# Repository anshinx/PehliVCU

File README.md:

# Pehlivan VCU (Vehicle Control Unit) - REVO.1 🏎️⚡

Trakya Üniversitesi Pehlivan Team ve Tas-Pro (Tasarım ve Proje Topluluğu) bünyesinde Shell Eco-marathon yarış aracı için özel olarak geliştirilmiş, endüstriyel standartlarda **Araç Kontrol Ünitesi (VCU)** donanım ve gömülü yazılım projesidir.

Bu kart; verimlilik, hafiflik ve kurşungeçirmez gürültü bağışıklığı (EMI/EMC) felsefesiyle, geleneksel ağır komponentlerin (lineer regülatörler, taş dirençler vb.) yerini tamamen akıllı yazılımsal ve anahtarlamalı çözümlere bırakması amacıyla sıfırdan tasarlanmıştır.

---

## 🛠️ Teknik Özellikler & Donanım Mimarisi

* **Ana İşlemci:** STM32G431 (ARM Cortex-M4 @170MHz, Matematik Hızlandırıcı CORDIC & FMAC).
* **Güç Girişi:** 12V - 14.4V Yarış Aküsü (Doğrudan besleme).
* **Periferi Beslemeleri:** * Yeni nesil yüksek verimli anahtarlamalı güç katı.
  * Nextion HMI, LoRa ve SD Kart modülleri için `100nF` seramik ve `10µF` kutuplu elektrolitik filtre kombinasyonlu izole besleme hatları.
* **Güç Çıkışları (Sürücü Katı):** `BTS432` Akıllı Güç Anahtarları (Far, Sinyal ve Fren Lambası kontrolü için).
* **Haberleşme & Telemetri:** * Doğrudan işlemciye bağlı LoRa Modülü (Kablosuz Telemetri).
  * Nextion HMI Ekran Arayüzü (UART).
  * FDCAN (Geriye dönük klasik CAN-Bus uyumlu, pitte maksimum esneklik).
* **Veri Günlüğü (Data Logging):** SD Kart Modülü üzerinden SPI haberleşmeli, anlık veri kaybını engelleyen "Kara Kutu" loglama altyapısı.
* **Zaman Senkronizasyonu:** CR2032/Düğme Pil destekli dahili RTC (Real Time Clock) mimarisi.

---

## ⚡ Donanım Tasarım Radikalleri (Neden REVO.1?)

REVO.1 revizyonu, pitteki kriz anlarını ve araç içi verimliliği maksimuma çıkarmak için şu kritik donanımsal kararlarla şekillendirilmiştir:

1. **Sıfır Taş Direnç / Sıfır Isı:** Şerit LED'lerin akım sınırlaması için kaba ve el yakan taş dirençler kullanılmamıştır. Akım kontrolü, STM32'nin Timer birimleri üzerinden **yazılımsal PWM (Sinyal Genişlik Modülasyonu)** ile çözülmüştür. Akü 14.4V'a vurduğunda lamba hatları `%83 Duty Cycle` ile kilitlenerek ortalama akım ideal 12V seviyesine çekilir.
2. **Yüksek Titreşim Dayanımı:** Kart üzerindeki 16 MHz harici kristal katında, yarış esnasındaki vibrasyondan bacakların yorulup kopmasını engellemek amacıyla bacaklı kılıflar yerine **Raltron 3225 4-SMD (RH100-16.000-18-2020-TR)** seramik kılıf tercih edilmiştir. Kristal yük kapasitesi ($C_L = 18\text{pF}$) hesaba katılarak hatlar `26pF` (veya `22pF`/`27pF`) kondansatörlerle stabilize edilmiştir.
3. **Parazit Bağışıklığı & Reset Koruması:** Araç içi motor sürücülerin ve yüksek akım hatlarının yaratacağı manyetik gürültülerden (EMI) korunmak için `NRST` (Reset) pini harici **10 kΩ dirençle `+3V3` hattına asılmış (Pull-Up)** ve `100nF` kondansatör ile şaseye filtrelenmiştir.
4. **Çift Katmanlı Bakır Havuzu:** Gürültü bağışıklığı için Bottom Layer tamamen kesintisiz `GND` bakır dolgusuyla kaplanmış, Top Layer ise STM32 etrafında `3V3` güç adalarıyla zırhlandırılmıştır.

---

## 🛰️ Gecikme (Latency) & Telemetri Lojiği

Kart üzerindeki pil destekli RTC donanımı, pit duvarı ile araç arasındaki LoRa veri transferinin gecikme süresini (latency) milisaniyelik çözünürlükle hesaplamak için kullanılır:
* Araç çalıştırılmadan önce bilgisayardan (veya Nextion üzerinden) Unix Epoch Time sinyaliyle RTC eşitlenir.
* VCU, LoRa paketini fırlatırken Unix zaman damgasının arkasına `HAL_GetTick()` değerinin son 3 basamağını ekler (`[UnixTimestamp].[Milisaniye]`).
* Pit tarafındaki alıcı yazılım, paketin varış zamanı ile paket içindeki zaman damgasını çıkararak hattaki milisaniyelik gecikmeyi anlık olarak raporlar.

---

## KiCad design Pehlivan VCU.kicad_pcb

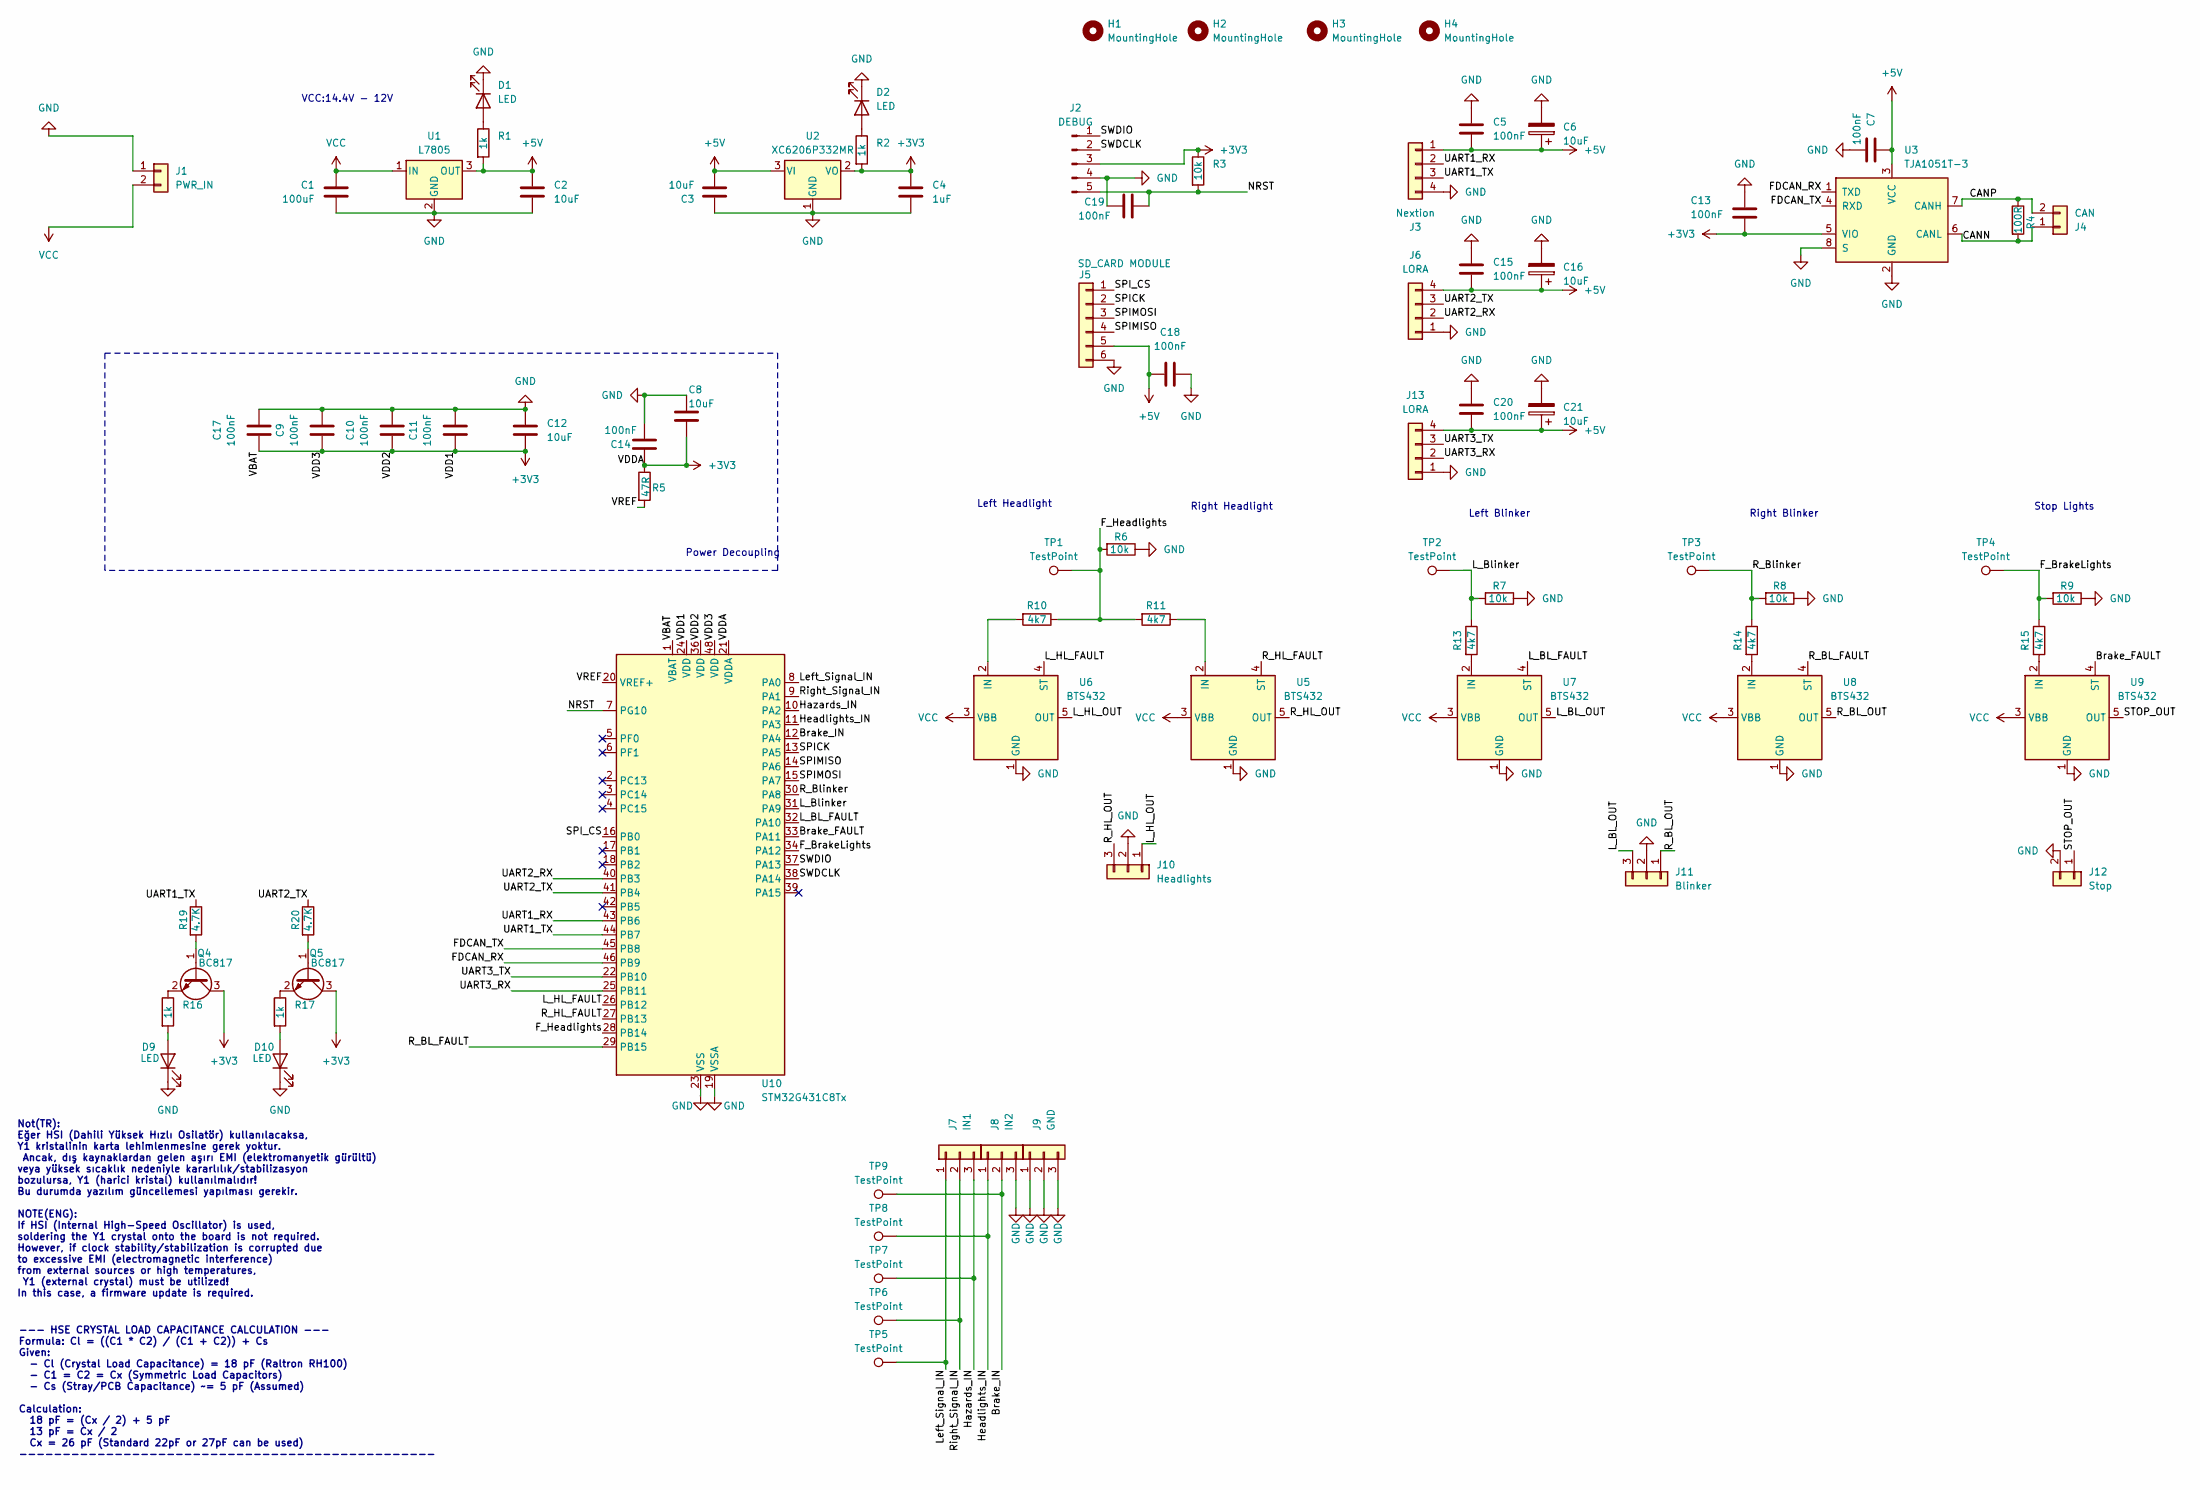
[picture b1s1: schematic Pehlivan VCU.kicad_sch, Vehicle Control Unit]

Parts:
C1: 100uF; C_Radial_D4.0mm_H7.0mm_P1.50mm
C2, C3, C6, C16, C21: 10uF; C_Radial_D5.0mm_H5.0mm_P2.00mm
C4: 1uF; C_Radial_D5.0mm_H5.0mm_P2.00mm
C5, C15, C18, C19, C20: 100nF; C_0805_2012Metric_Pad1.18x1.45mm_HandSolder
C7, C13: 100nF; C_1210_3225Metric_Pad1.33x2.70mm_HandSolder
C8: 10uF; C_0805_2012Metric_Pad1.18x1.45mm_HandSolder
C9, C10, C11, C14, C17: 100nF; C_0603_1608Metric
C12: 10uF; C_1210_3225Metric_Pad1.33x2.70mm_HandSolder
D1, D2, D9, D10: LED; LED_1206_3216Metric_Pad1.42x1.75mm_HandSolder
H1, H2, H3, H4: MountingHole; MountingHole_2.7mm_M2.5_DIN965_Pad
J1: PWR_IN; TerminalBlock_Phoenix_MKDS-1,5-2-5.08_1x02_P5.08mm_Horizont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
J2: DEBUG; PinHeader_1x05_P2.54mm_Vertical
J3: Nextion; TerminalBlock_Phoenix_MKDS-1,5-4-5.08_1x04_P5.08mm_Horizont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
J4: CAN; TerminalBlock_Phoenix_MKDS-1,5-2-5.08_1x02_P5.08mm_Horizont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
J5: SD_CARD MODULE; PinSocket_1x06_P2.54mm_Vertical
J6, J13: LORA; PinSocket_1x04_P2.54mm_Horizontal
J7: IN1; TerminalBlock_Phoenix_MKDS-1,5-3-5.08_1x03_P5.08mm_Horizont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
J8: IN2; TerminalBlock_Phoenix_MKDS-1,5-3-5.08_1x03_P5.08mm_Horizont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
J9: GND; TerminalBlock_Phoenix_MKDS-1,5-3-5.08_1x03_P5.08mm_Horizont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
J10: Headlights; TerminalBlock_Phoenix_MKDS-1,5-3-5.08_1x03_P5.08mm_Horizont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
J11: Blinker; TerminalBlock_Phoenix_MKDS-1,5-3-5.08_1x03_P5.08mm_Horizont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
J12: Stop; TerminalBlock_Phoenix_MKDS-1,5-2-5.08_1x02_P5.08mm_Horizont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
Q4, Q5: BC817; SOT-23
R1, R2, R16, R17: 1k; R_0805_2012Metric
R3, R6, R7, R8, R9: 10k; R_0805_2012Metric
R4: 100R; R_0805_2012Metric
R5: 47R; R_0603_1608Metric_Pad0.98x0.95mm_HandSolder
R10, R11, R13, R14, R15: 4k7; R_0805_2012Metric
R19, R20: 4.7K; R_0805_2012Metric_Pad1.20x1.40mm_HandSolder
TP1, TP2, TP3, TP4, TP5, TP6, TP7, TP8, TP9: TestPoint; TestPoint_Pad_D1.0mm
U1: L7805; TO-220-3_Vertical
U2: XC6206P332MR; SOT-23-3
U3: TJA1051T-3; SOIC-8_3.9x4.9mm_P1.27mm
U5, U6, U7, U8, U9: BTS432; TO-263-4
U10: STM32G431C8Tx; LQFP-48_7x7mm_P0.5mm

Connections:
+3V3: C4.1, C8.2, C9.1, C10.1, C11.1, C12.2, C13.2, C14.1, C17.1, J2.3, Q4.3 (C), Q5.3 (C), R2.2, R3.1, R5.1, U2.2 (VO), U3.5 (VIO), U10.1 (VBAT), U10.21 (VDDA), U10.24 (VDD), U10.36 (VDD), U10.48 (VDD)
+5V: C2.1, C3.1, C5.2, C6.1, C7.1, C15.2, C16.1, C18.2, C20.2, C21.1, J3.1, J5.5, J6.4, J13.4, R1.2, U1.3 (OUT), U2.3 (VI), U3.3 (VCC)
/Brake_FAULT: U9.4 (ST), U10.33 (PA11)
/Brake_IN: J8.2, TP9.1 (1_1), U10.12 (PA4)
/CANN: J4.1, R4.2, U3.6 (CANL)
/CANP: J4.2, R4.1, U3.7 (CANH)
/FDCAN_RX: U3.1 (TXD), U10.46 (PB9)
/FDCAN_TX: U3.4 (RXD), U10.45 (PB8)
/F_BrakeLights: R9.2, R15.1, TP4.1 (1_1), U10.34 (PA12)
/F_Headlights: R6.2, R10.1, R11.2, TP1.1 (1_1), U10.28 (PB14)
/Hazards_IN: J7.3, TP7.1 (1_1), U10.10 (PA2)
/Headlights_IN: J8.1, TP8.1 (1_1), U10.11 (PA3)
/L_BL_FAULT: U7.4 (ST), U10.32 (PA10)
/L_BL_OUT: J11.3, U7.5 (OUT)
/L_Blinker: R7.2, R13.1, TP2.1 (1_1), U10.31 (PA9)
/L_HL_FAULT: U6.4 (ST), U10.26 (PB12)
/L_HL_OUT: J10.1, U6.5 (OUT)
/Left_Signal_IN: J7.1, TP5.1 (1_1), U10.8 (PA0)
/NRST: C19.1, J2.5, R3.2, U10.7 (PG10)
/R_BL_FAULT: U8.4 (ST), U10.29 (PB15)
/R_BL_OUT: J11.1, U8.5 (OUT)
/R_Blinker: R8.2, R14.1, TP3.1 (1_1), U10.30 (PA8)
/R_HL_FAULT: U5.4 (ST), U10.27 (PB13)
/R_HL_OUT: J10.3, U5.5 (OUT)
/Right_Signal_IN: J7.2, TP6.1 (1_1), U10.9 (PA1)
/SPICK: J5.2, U10.13 (PA5)
/SPIMISO: J5.4, U10.14 (PA6)
/SPIMOSI: J5.3, U10.15 (PA7)
/SPI_CS: J5.1, U10.16 (PB0)
/STOP_OUT: J12.1, U9.5 (OUT)
/SWDCLK: J2.2, U10.38 (PA14)
/SWDIO: J2.1, U10.37 (PA13)
/UART1_RX: J3.2, U10.43 (PB6)
/UART1_TX: J3.3, R19.1, U10.44 (PB7)
/UART2_RX: J6.2, U10.40 (PB3)
/UART2_TX: J6.3, R20.1, U10.41 (PB4)
/UART3_RX: J13.2, U10.25 (PB11)
/UART3_TX: J13.3, U10.22 (PB10)
/VREF: R5.2, U10.20 (VREF+)
GND: C1.2, C2.2, C3.2, C4.2, C5.1, C6.2, C7.2, C8.1, C9.2, C10.2, C11.2, C12.1, C13.1, C14.2, C15.1, C16.2, C17.2, C18.1, C19.2, C20.1, C21.2, D1.1 (K), D2.1 (K), D9.1 (K), D10.1 (K), J1.1, J2.4, J3.4, J5.6, J6.1, J8.3, J9.1, J9.2, J9.3, J10.2, J11.2, J12.2, J13.1, R6.1, R7.1, R8.1, R9.1, U1.2 (GND), U2.1 (GND), U3.2 (GND), U3.8 (S), U5.1 (GND), U6.1 (GND), U7.1 (GND), U8.1 (GND), U9.1 (GND), U10.19 (VSSA), U10.23 (VSS), U10.35 (VSS), U10.47 (VSS)
unnamed: D1.2 (A), R1.1
unnamed: D2.2 (A), R2.1
unnamed: D9.2 (A), R16.2
unnamed: D10.2 (A), R17.2
unnamed: Q4.1 (B), R19.2
unnamed: Q4.2 (E), R16.1
unnamed: Q5.1 (B), R20.2
unnamed: Q5.2 (E), R17.1
unnamed: R11.1, U5.2 (IN)
unnamed: R10.2, U6.2 (IN)
unnamed: R13.2, U7.2 (IN)
unnamed: R14.2, U8.2 (IN)
unnamed: R15.2, U9.2 (IN)
VCC: C1.1, J1.2, U1.1 (IN), U5.3 (VBB), U6.3 (VBB), U7.3 (VBB), U8.3 (VBB), U9.3 (VBB)

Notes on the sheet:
Stop Lights
Right Headlight
Left Blinker
Right Blinker
--- HSE CRYSTAL LOAD CAPACITANCE CALCULATION --- Formula: Cl = ((C1 * C2) / (C1 + C2)) + Cs Given: - Cl (Crystal Load Capacitance) = 18 pF (Raltron RH100) - C1 = C2 = Cx (Symmetric Load Capacitors) - Cs (Stray/PCB Capacitance) ~= 5 pF (Assumed) Calculation: 18 pF = (Cx / 2) + 5 pF 13 pF = Cx / 2 Cx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
VCC:14.4V - 12V
Left Headlight
Not(TR): Eğer HSI (Dahili Yüksek Hızlı Osilatör) kullanılacaksa, Y1 kristalinin karta lehimlenmesine gerek yoktur. Ancak, dış kaynaklardan gelen aşırı EMI (elektromanyetik gürültü) veya yüksek sıcaklık nedeniyle kararlılık/stabilizasyon bozulursa, Y1 (harici kristal) kullanılmalıdır! Bu durumda yaz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
Power Decoupling

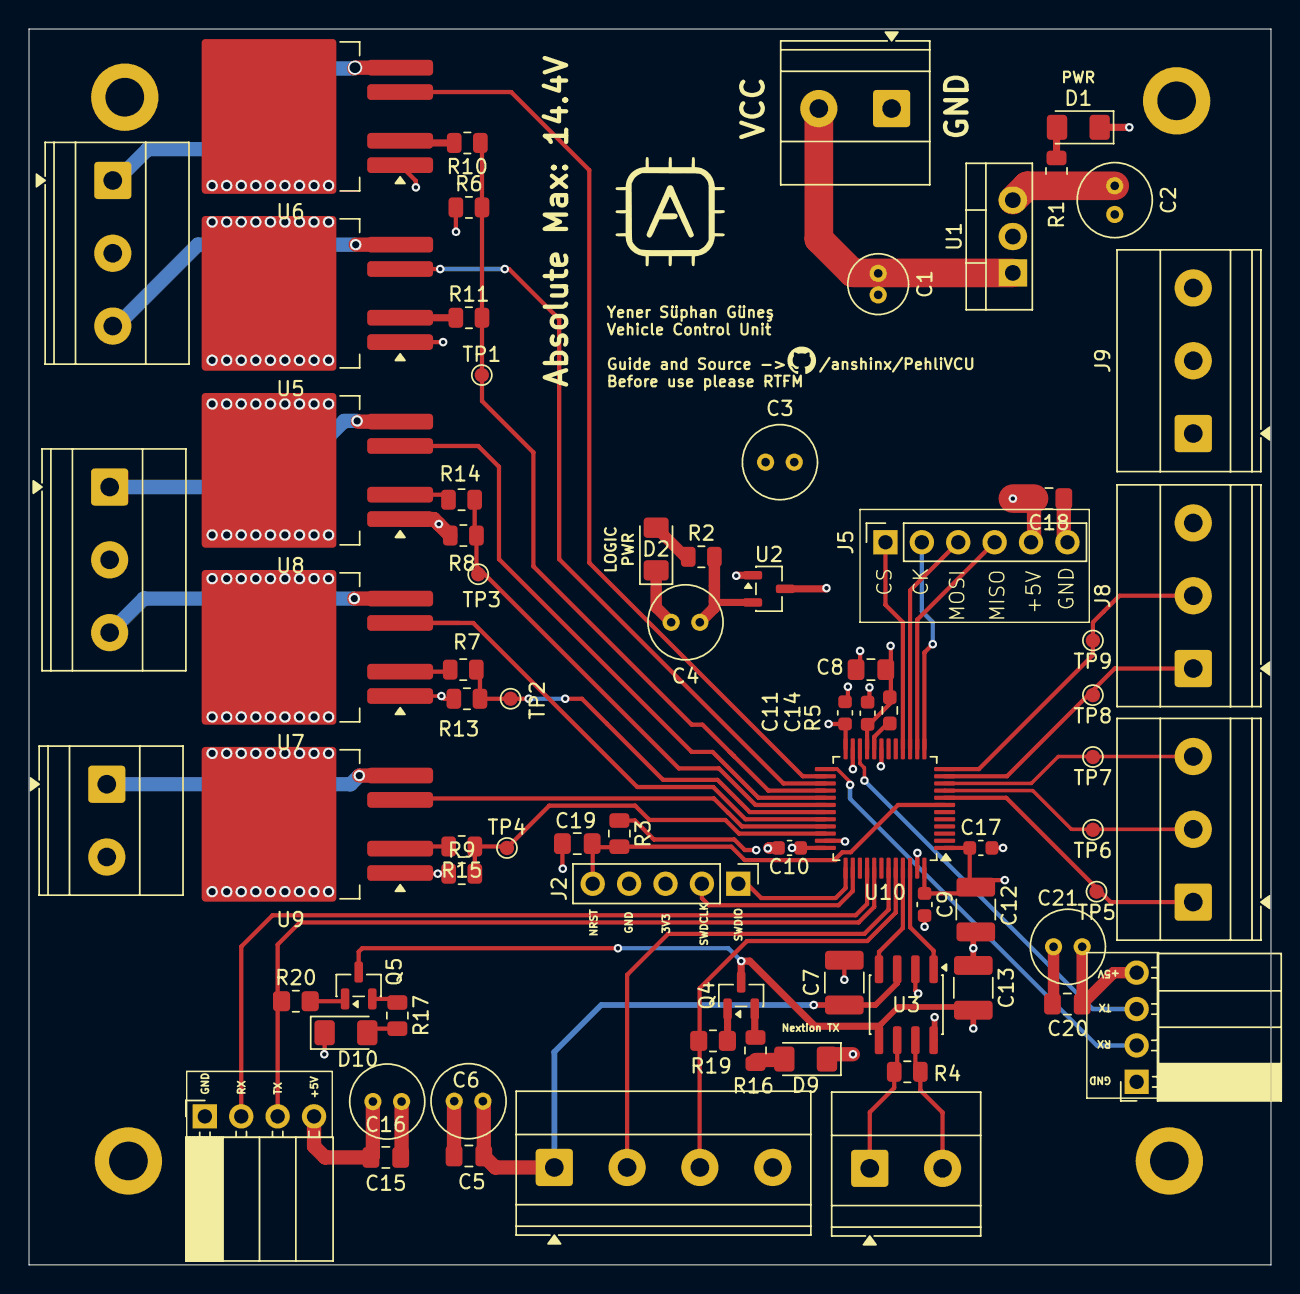
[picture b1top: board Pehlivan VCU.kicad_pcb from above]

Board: 4 copper layers, 86.7 x 86.2 mm, 80 parts (0 on the bottom side), 54 nets.

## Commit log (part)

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2026-06-13 rev.0.1
2026-06-13 Initialize README with project details and specifications
    Added detailed project description, technical specifications, and design rationale for the Pehlivan VCU.
